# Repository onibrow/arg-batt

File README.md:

# Arias Research Group - Battery Testing Board

### Seiya Ono Sp'19

## Overview

The board was designed such that the Photon could both drive and discharge the battery cell attached. The battery load resistor was chosen to be 0805 SMD so it could potentially be upgraded to handle higher discharges. Other than that, there are redundant connectors coming off so the user can access needed pins in different ways. The board also features two exposed test pads to probe the resistance of the load resistor precisely, given the user measures it before soldering on the Photon.

The pins below the Photon as well as the battery connection pins are meant for test points. The slide switch can disconnect the battery from the circuit as to not discharge when unnecessary. There are 5 indicator LEDs on the side that can be programmed by the user.

The BOM can be found as `bom.csv` and includes the parts used to populate the board.

### Resistor Selection

The [10 Ohm Resistor](https://www.digikey.com/product-detail/en/stackpole-electronics-inc/RNCF0805AKT10R0/RNCF0805AKT10R0CT-ND/4250701) was chosen by searching through Digikey with [these filters](https://www.digikey.com/products/en/resistors/chip-resistor-surface-mount/52?k=&pkeyword=&sv=0&pv7=2&pv1989=0&pv3=651&pv3=667&pv3=696&pv16=39329&pv1127=i2&sf=1&FV=-8%7C52&quantity=&ColumnSort=0&page=1&stock=1&nstock=1&photo=1&pageSize=50) enabled.

If that link somehow is broken, the filters are as follows:

`Product Index > Resistors > Chip Resistor > Surface Mount`

Part Status: Active

Package / Case: 0805

Packaging: Cut Tape

Tolerance: 0.01%, 0.02%, 0.05%

Number of Terminations: 2

In stock: Checked

Normally Stocking: Checked

Photo: Checked

## Tips

When soldering, start with the smallest components, as they are the hardest to solder. Then move to the test points and slide switch, then the Photon. When soldering the Photon, make sure it is aligned well so that all the pads have enough room to contact the castelated board.

## Specifications

From Dr. Evans:

Idea is to carry out multi-cycle testing of a Panasonic coin cell (about 3 million cycles). With the present arrangement (a Photon mounted on a breadboard) we have reached ~ 2 million cycles and still going. The design connects the DAC output of the Photon (nominally 0 – 3.3V DC) to the positive terminal of the cell holder via a 10 Ohm resistor. The negative terminal of the cell holder is connected to GND on the Photon. Wires run from either side of the resistor to the analog input connections on the Photon so that the current can be determined from the voltage drop across the resistor (A3 to A5) and the cell voltage determined by one of the connections (A3). We have software that brings the DAC output to greater than the cell voltage during charge and lowers it to below cell voltage during discharge. A cycle takes approximately 400 ms and the data are relayed via Webhook to ThingSpeak (Math Works’ version of the cloud) for plotting/analysis.

### Task

1. Build present design but with soldered connections. Two Photons without header pins should be here by next week. We have cell holders and cells.
1. Set up the Photons and load code (I will supply).
1. Run a couple of cells to 3 million cycles or failure, collecting data.
1. See what we can do next.

Useful Links:

[Photon](https://store.particle.io/products/photon)

## Possibilities

* External power - through maybe a barrel jack to provide external power to the entire board, so that the photon's uUSB isn't stressed
* Push buttons for Photon configuration - allows external user to set up and start different testing procedures
* Accurate ammeter for measuring current.
* Instead of having a soldered on resistor, can use [SIP Sockets](https://www.digikey.com/product-detail/en/mill-max-manufacturing-corp/346-43-102-41-013000/ED6464-02-ND/1212288) to make impermanent connections with precision through hole resistors. This way, they can be swapped in and out for future proofing.

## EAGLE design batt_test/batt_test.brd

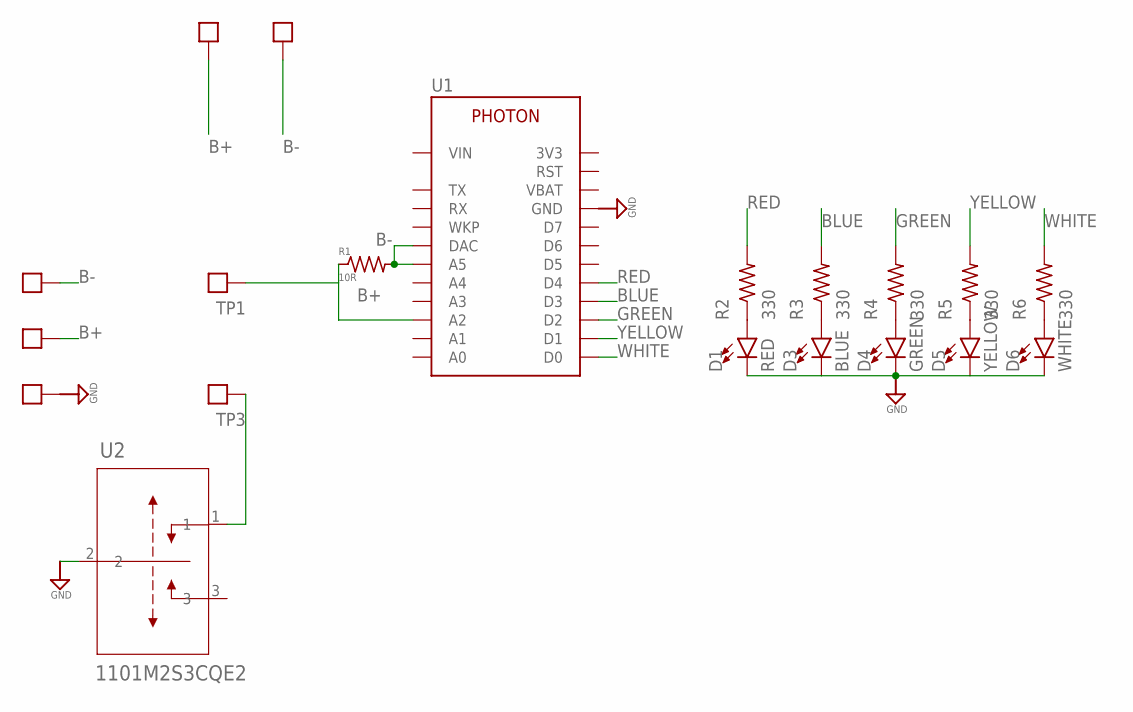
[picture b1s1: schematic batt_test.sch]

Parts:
B+: TEST_POINTTHRU; TEST_POINT
B-: TEST_POINT; TEST_POINT-1206
B-2: TEST_POINTTHRU; TEST_POINT
D1: RED; LED-0603
D3: BLUE; LED-0603
D4: GREEN; LED-0603
D5: YELLOW; LED-0603
D6: WHITE; LED-0603
POS: TEST_POINT; TEST_POINT-1206
R1: 10R; R0805
R2, R3, R4, R5, R6: 330; R0402
TP1, TP2, TP3: TEST_POINTTHRU; TEST_POINT
U1: PHOTON
U2: 1101M2S3CQE2

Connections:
B+: B+.1, POS.1, R1.1, TP1.1, U1.A2
B-: B-.1, B-2.1, R1.2, U1.A5, U1.DAC
BLUE: R3.2, U1.D3
GND: D1.C, D3.C, D4.C, D5.C, D6.C, TP2.1, U1.GND, U1.GND@1 (GND), U2.2
GREEN: R4.2, U1.D2
unnamed: TP3.1, U2.1
unnamed: D1.A, R2.1
unnamed: D3.A, R3.1
unnamed: D4.A, R4.1
unnamed: D5.A, R5.1
unnamed: D6.A, R6.1
RED: R2.2, U1.D4
WHITE: R6.2, U1.D0
YELLOW: R5.2, U1.D1

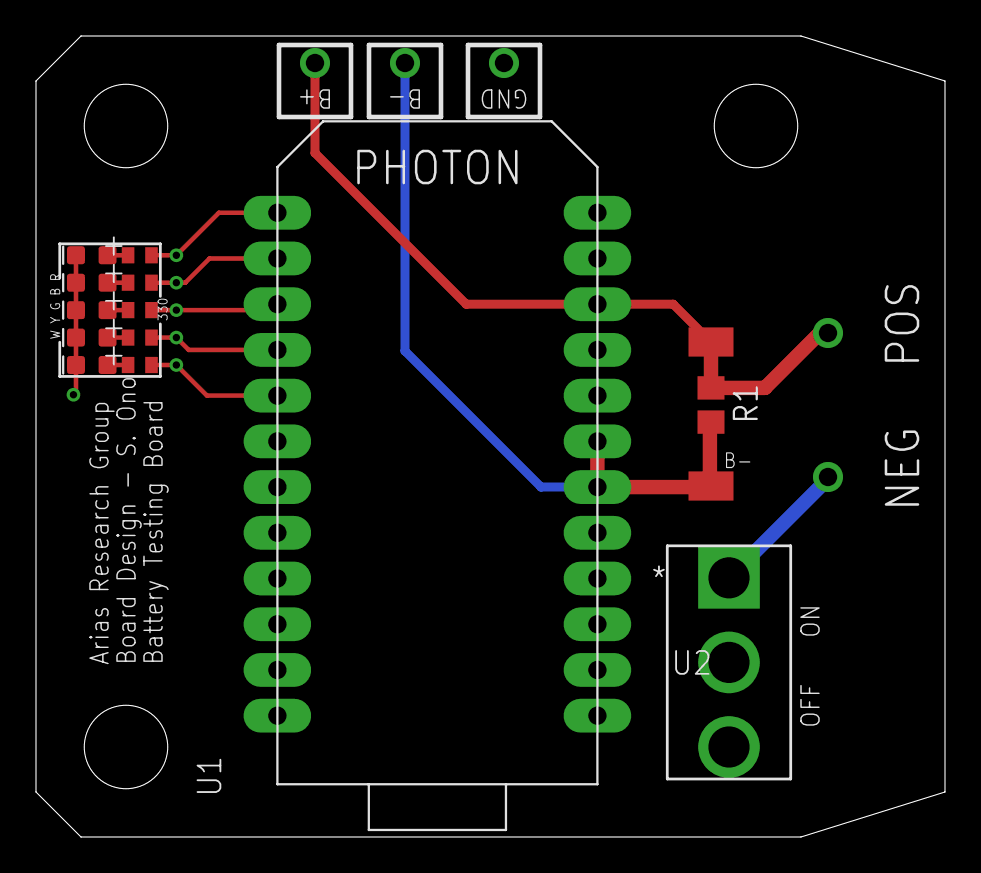
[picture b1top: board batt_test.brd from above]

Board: 2 copper layers, 50.5 x 44.5 mm, 23 parts (0 on the bottom side), 14 nets.

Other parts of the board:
U$1, U$3, U$4: 4-40-HOLE

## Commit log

2019-03-15 initialize project
2019-03-15 add pic
2019-03-15 Add some notes
2019-03-17 start schematic
2019-03-17 start board layout
2019-03-18 add batt test point
2019-03-18 finish first proto
2019-03-19 add bom
2019-04-29 update bom and gerber
2019-05-02 new contacts and bom
2019-05-17 serial extraction
2020-02-14 one last time?
2020-04-10 final revision push
